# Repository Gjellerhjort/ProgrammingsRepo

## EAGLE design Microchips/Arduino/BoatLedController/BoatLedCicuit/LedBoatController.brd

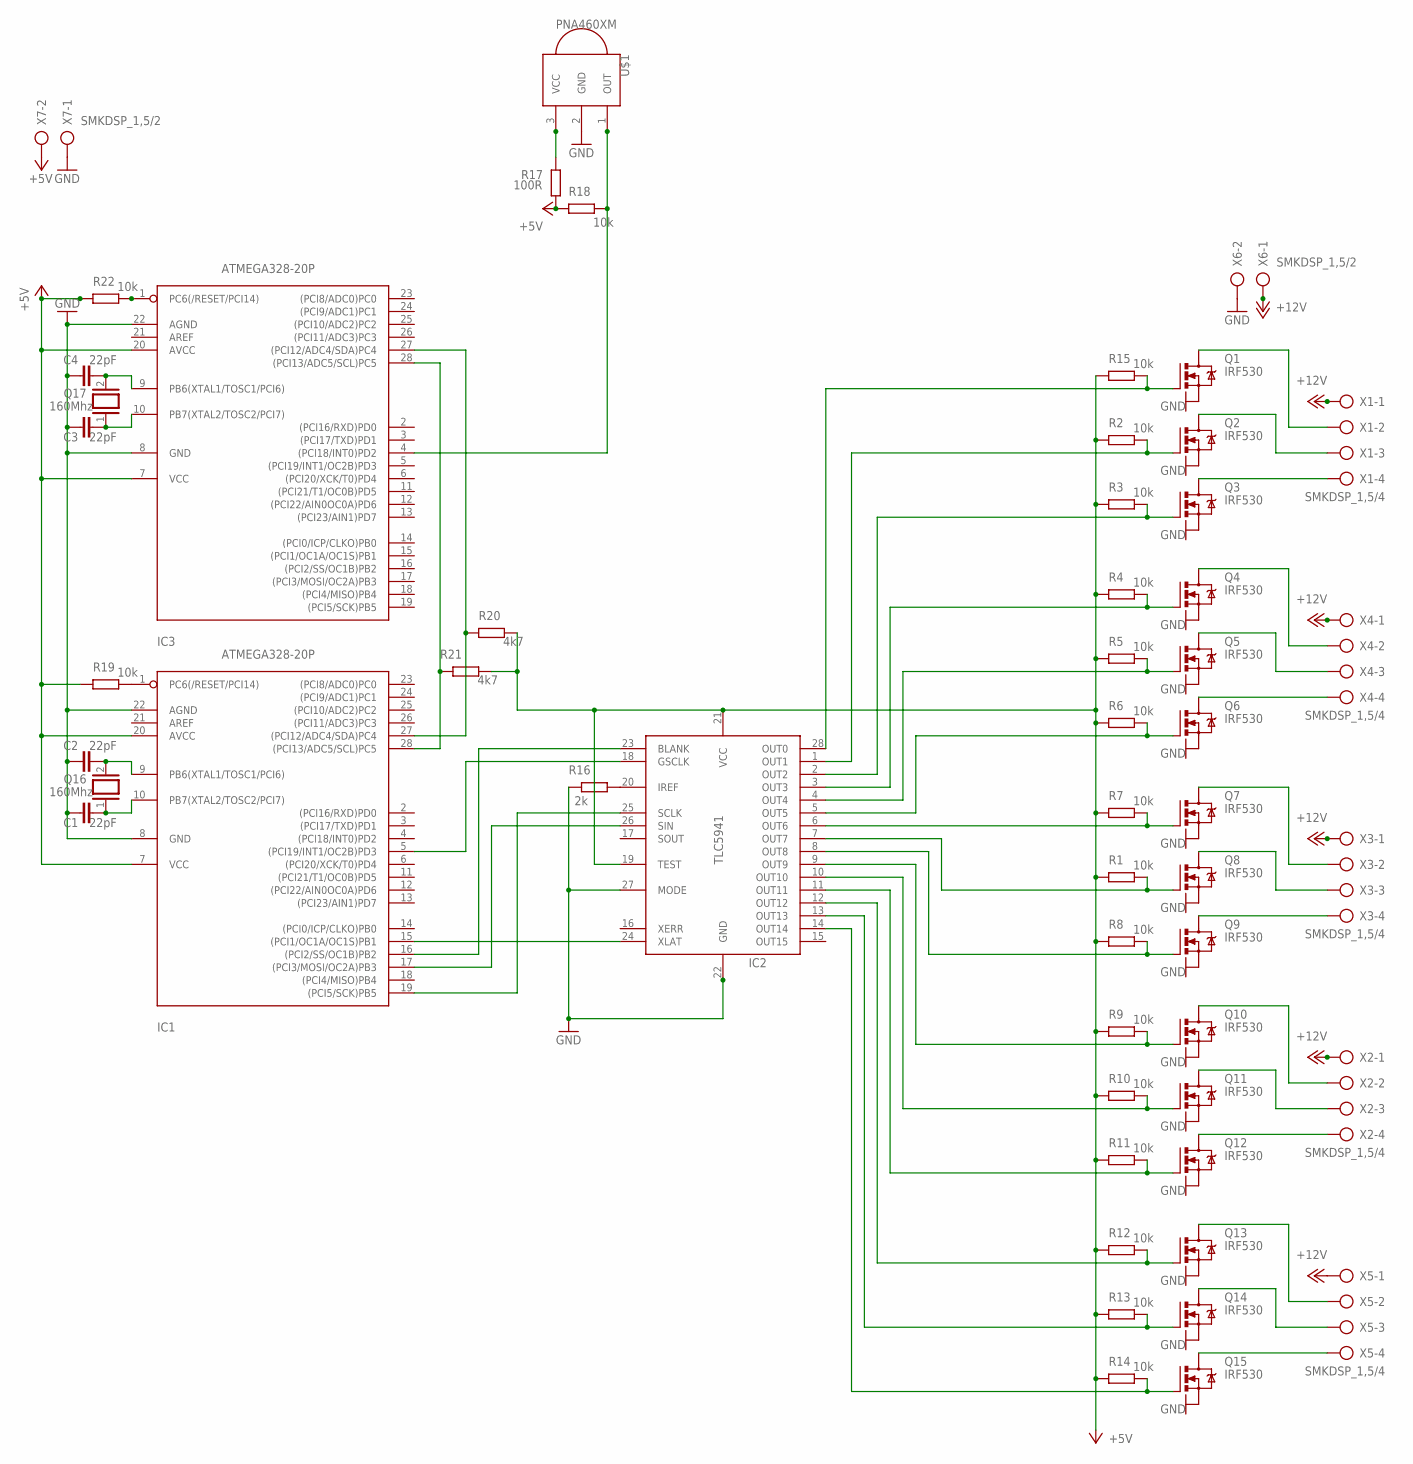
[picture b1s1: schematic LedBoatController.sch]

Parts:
C1, C2, C3, C4: 22pF; CAP-PTH-2.54
IC1, IC3: ATMEGA328-20P; DIL28-3
IC2: TLC5941NT; DIL28-3
Q1, Q2, Q3, Q4, Q5, Q6, Q7, Q8, Q9, Q10, Q11, Q12, Q13, Q14, Q15: IRF530; TO220BV
Q16, Q17: 160Mhz; QS
R1, R2, R3, R4, R5, R6, R7, R8, R9, R10, R11, R12, R13, R14, R15, R18, R19, R22: 10k; 0207/10
R16: 2k; 0207/10
R17: 100R; 0207/10
R20, R21: 4k7; 0207/10
U$1: PNA460XM
X1, X2, X3, X4, X5: SMKDSP_1,5/4
X6, X7: SMKDSP_1,5/2

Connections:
+5V: IC1.7 (VCC), IC1.20 (AVCC), IC2.19 (TEST), IC2.21 (VCC), IC3.7 (VCC), IC3.20 (AVCC), R1.2, R2.2, R3.2, R4.2, R5.2, R6.2, R7.2, R8.2, R9.2, R10.2, R11.2, R12.2, R13.2, R14.2, R15.2, R17.2, R18.2, R19.2, R20.2, R21.2, R22.2, X7.2
+12V: X1.1, X2.1, X3.1, X4.1, X5.1, X6.1
GND: C1.1, C2.1, C3.1, C4.1, IC1.8 (GND), IC1.22 (AGND), IC2.22 (GND), IC2.27 (MODE), IC3.8 (GND), IC3.22 (AGND), Q1.S, Q2.S, Q3.S, Q4.S, Q5.S, Q6.S, Q7.S, Q8.S, Q9.S, Q10.S, Q11.S, Q12.S, Q13.S, Q14.S, Q15.S, R16.2, U$1.2 (GND), X6.2, X7.1
unnamed: IC2.28 (OUT0), Q1.G, R15.1
unnamed: C1.2, IC1.10 (PB7(XTAL2/TOSC2/PCI7)), Q16.1
unnamed: IC2.1 (OUT1), Q2.G, R2.1
unnamed: IC2.2 (OUT2), Q3.G, R3.1
unnamed: IC2.3 (OUT3), Q4.G, R4.1
unnamed: IC2.4 (OUT4), Q5.G, R5.1
unnamed: IC2.5 (OUT5), Q6.G, R6.1
unnamed: IC2.6 (OUT6), Q7.G, R7.1
unnamed: IC2.7 (OUT7), Q8.G, R1.1
unnamed: IC2.8 (OUT8), Q9.G, R8.1
unnamed: IC2.9 (OUT9), Q10.G, R9.1
unnamed: IC2.10 (OUT10), Q11.G, R10.1
unnamed: IC2.11 (OUT11), Q12.G, R11.1
unnamed: IC2.12 (OUT12), Q13.G, R12.1
unnamed: IC2.13 (OUT13), Q14.G, R13.1
unnamed: IC2.14 (OUT14), Q15.G, R14.1
unnamed: Q15.D, X5.4
unnamed: Q14.D, X5.3
unnamed: Q13.D, X5.2
unnamed: Q12.D, X2.4
unnamed: Q11.D, X2.3
unnamed: Q10.D, X2.2
unnamed: Q9.D, X3.4
unnamed: Q8.D, X3.3
unnamed: Q7.D, X3.2
unnamed: Q6.D, X4.4
unnamed: Q5.D, X4.3
unnamed: Q4.D, X4.2
unnamed: Q3.D, X1.4
unnamed: Q2.D, X1.3
unnamed: Q1.D, X1.2
unnamed: C2.2, IC1.9 (PB6(XTAL1/TOSC1/PCI6)), Q16.2
unnamed: IC1.15 ((PCI1/OC1A/OC1S)PB1), IC2.24 (XLAT)
unnamed: IC1.17 ((PCI3/MOSI/OC2A)PB3), IC2.26 (SIN)
unnamed: IC1.16 ((PCI2/SS/OC1B)PB2), IC2.23 (BLANK)
unnamed: IC1.19 ((PCI5/SCK)PB5), IC2.25 (SCLK)
unnamed: IC2.20 (IREF), R16.1
unnamed: IC1.1 (PC6(/RESET/PCI14)), R19.1
unnamed: IC1.5 ((PCI19/INT1/OC2B)PD3), IC2.18 (GSCLK)
unnamed: R17.1, U$1.3 (VCC)
unnamed: C3.2, IC3.10 (PB7(XTAL2/TOSC2/PCI7)), Q17.1
unnamed: C4.2, IC3.9 (PB6(XTAL1/TOSC1/PCI6)), Q17.2
unnamed: IC1.27 ((PCI12/ADC4/SDA)PC4), IC3.27 ((PCI12/ADC4/SDA)PC4), R20.1
unnamed: IC3.1 (PC6(/RESET/PCI14)), R22.1
unnamed: IC3.4 ((PCI18/INT0)PD2), R18.1, U$1.1 (OUT)
unnamed: IC1.28 ((PCI13/ADC5/SCL)PC5), IC3.28 ((PCI13/ADC5/SCL)PC5), R21.1

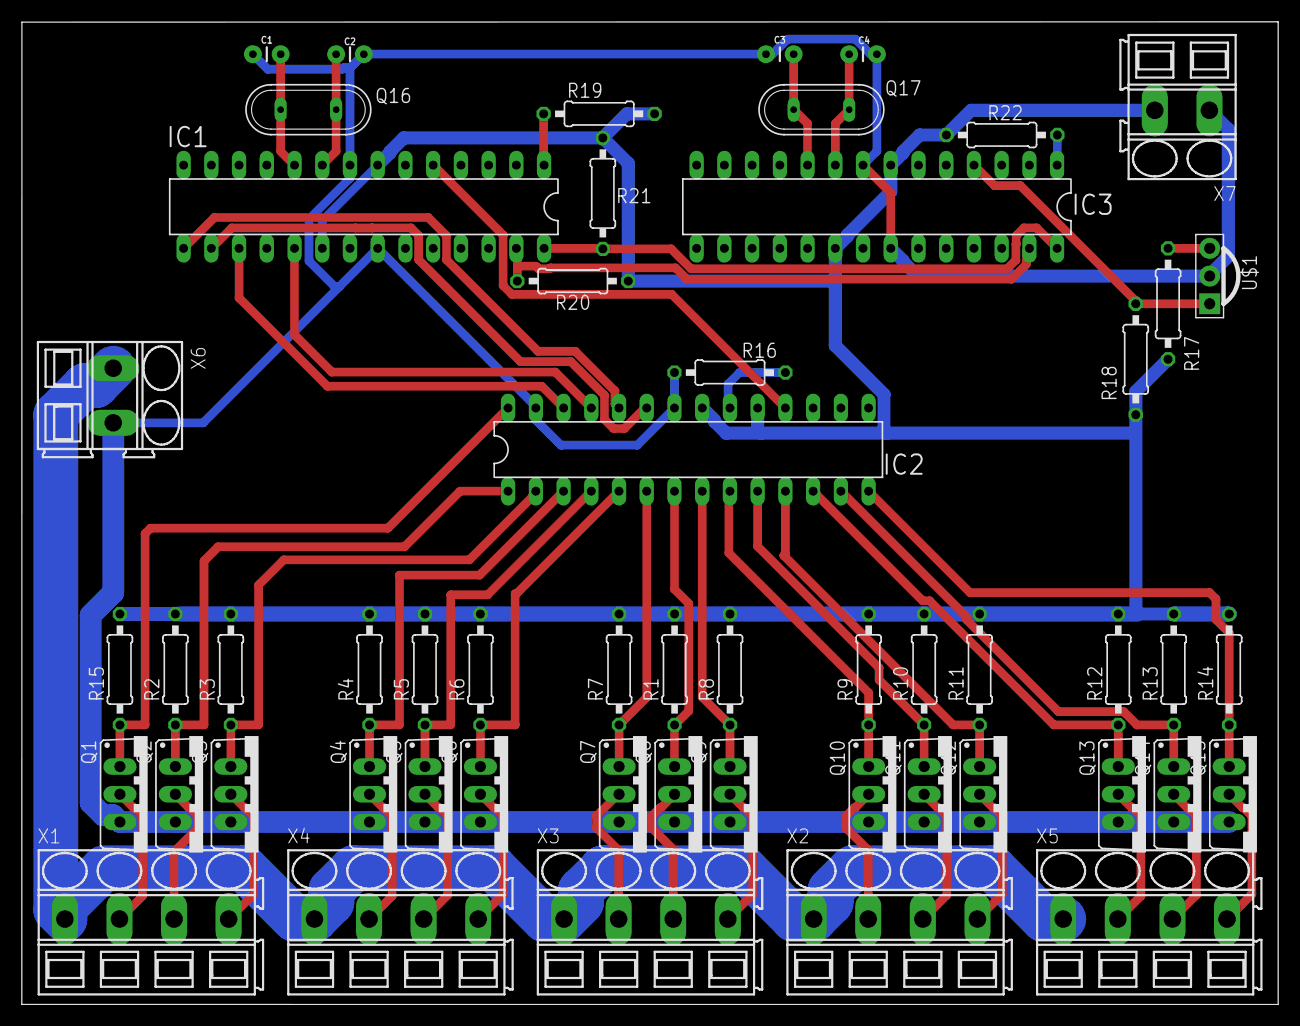
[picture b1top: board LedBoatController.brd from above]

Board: 2 copper layers, 115.1 x 90.0 mm, 54 parts (0 on the bottom side), 49 nets.

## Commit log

2023-05-24 Opgave 1 fininsh or?
2023-05-24 Opgave 1 small change
2023-05-25 Yes one more lets gooo
2023-05-25 Made assignment 5 Calculator
2023-05-25 Made a web version of the calculator
2023-05-26 arduino
2023-05-26 somwthing
2023-05-28 Working
2023-05-30 made circuit diagram
2023-06-06 made more stuff
2023-06-06 New stuff
2023-07-02 update it all
2023-07-05 somestuff
2023-07-05 Added Embeded C
2023-07-05 fixed CarValveSystem.ino code
2023-07-05 more programs
2023-07-05 made som codewars challenges
2023-07-06 made some more codewars challenges
2023-07-10 not finish
2023-09-22 some python programming
2024-03-16 solved write number in expanded form on codewars
2024-08-18 start
2024-08-19 working scrape func and cheapest food with little bug
2024-09-06 nye opgaver
2024-09-06 fixed tic tac toe
2024-09-06 game working
2024-09-11 game remove test line
2024-09-11 small changes
2024-09-19 finish all task for 1
2024-09-23 more tasks
2024-10-21 big changes
2024-10-26 fixed stuff
2024-10-27 finish more tasks
2024-10-28 drop files from .gitignore
2024-11-07 fixed and made somestuff
2024-11-21 started on workshop 10
2024-11-21 more stuff made on workshop 10
2024-12-01 Rename Readme.md to README.md
    trw
2025-01-04 created a fpga folder and finish lektion 6 all ext have code and sim
2025-01-04 lektion 8 finish some ext have code and sim
2025-01-05 lektion 9 some ext have code and sim
2025-01-05 lektion 8 some ext have code and sim
2025-01-06 meget mere
2025-01-07 lektion 9 opgave 2
2025-01-07 lektion 10
2025-03-21 fix this mess
2025-03-21 cleagning
2025-03-21 more cleaning
2025-03-21 more stuff
2025-05-09 something
2025-05-11 clean up
2025-06-13 3d model for opgave 1.2 in workshop 2
2025-06-18 idk having fun
2025-06-20 STM boards
2025-06-28 ignore secrets.h
2025-06-28 added some stuff
2025-06-30 stm32
2025-09-14 some more stuff
2025-09-25 lul
    i need help
2025-10-11 rename and some small changes
2025-10-11 more
2025-10-11 mm7 exercise 1

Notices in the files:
parts and their libraries:
SparkFun-Capacitors: Licensing: Creative Commons ShareAlike 4.0 International - https://creativecommons.org/licenses/by-sa/4.0
